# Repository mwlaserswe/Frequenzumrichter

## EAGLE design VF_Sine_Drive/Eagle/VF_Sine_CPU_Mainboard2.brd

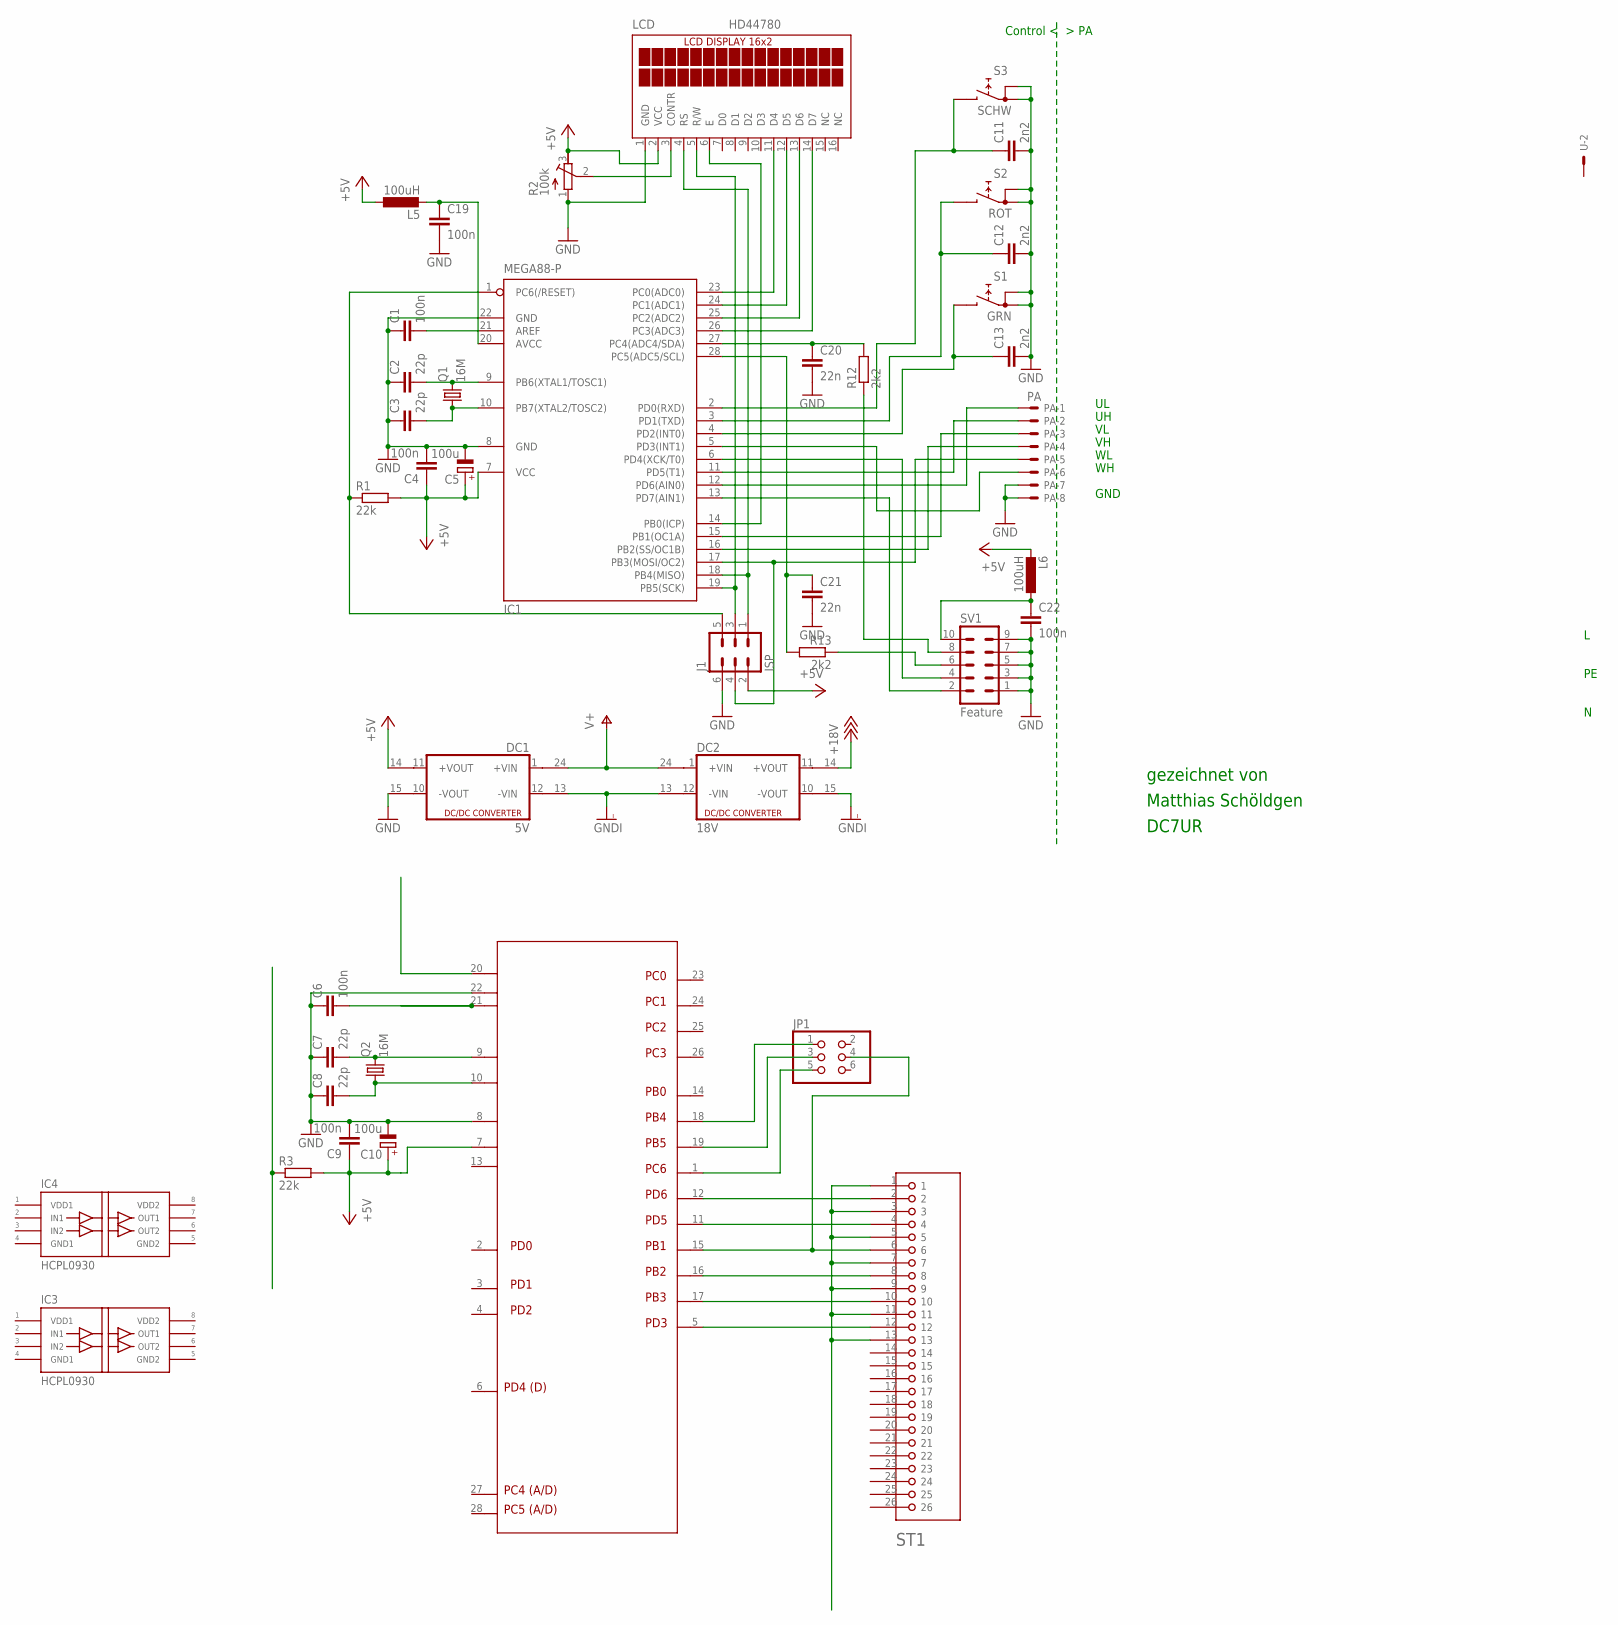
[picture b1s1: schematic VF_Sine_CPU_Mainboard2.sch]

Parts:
C1, C4, C6, C9, C22: 100n; C025-025X050
C2, C3, C7, C8: 22p; C025-025X050
C5, C10: 100u; B45181A
C11, C12, C13: 2n2; C025-025X050
C19: 100n; C050-030X075
C20, C21: 22n; C025-024X044
DC1: 5V; CMK
DC2: 18V; CMK
IC1: MEGA88-P; DIL28-3
IC2: ATMEGA328P_VAR; DIL-28S
IC3, IC4: HCPL0930; SO8
J1: ISP; ML6
JP1: PINHD-2X3; 2X03
L5, L6: 100uH; 0204/5
LCD: HD44780; TUXGR_16X2_R2
PA: PA; 22-23-2081
Q1, Q2: 16M; HC49/S
R1, R3: 22k; 0207/2V
R2: 100k; RTRIM4G/J
R12, R13: 2k2; 0204/5
S1: GRN; RDT1034
S2: ROT; RDT1034
S3: SCHW; RDT1034
ST1: HD-26
SV1: Feature; ML10
U: 5566-2

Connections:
+5V: C4.1, C5.+, C9.1, C10.+, DC1.14 (+VOUT1), IC1.7 (VCC), IC2.7, J1.2, L5.1, L6.2, LCD.2 (VCC), R1.2, R2.3 (A), R3.2
+18V: DC2.14 (+VOUT1)
GND: C1.1, C2.1, C3.1, C4.2, C5.-, C6.1, C7.1, C8.1, C9.2, C10.-, C11.2, C12.2, C13.2, C19.2, C20.2, C21.2, C22.2, DC1.15 (-VOUT1), IC1.8 (GND), IC1.22 (GND), IC2.8, IC2.22, J1.6, LCD.1 (GND), PA.7, PA.8, R2.1 (E), S1.A, S1.A1, S2.A, S2.A1, S3.A, S3.A1, SV1.1, SV1.3, SV1.5, SV1.7, SV1.9
GNDI: DC1.13 (-VIN1), DC2.13 (-VIN1), DC2.15 (-VOUT1)
unnamed: IC1.18 (PB4(MISO)), J1.1, LCD.4 (RS)
unnamed: IC1.19 (PB5(SCK)), J1.3, LCD.5 (R/W)
unnamed: IC1.17 (PB3(MOSI/OC2)), J1.4, PA.5
unnamed: IC1.1 (PC6(/RESET)), J1.5, R1.1
unnamed: IC1.12 (PD6(AIN0)), PA.1
unnamed: IC1.11 (PD5(T1)), PA.2
unnamed: IC1.15 (PB1(OC1A)), PA.3
unnamed: IC1.16 (PB2(SS/OC1B)), PA.4
unnamed: IC1.5 (PD3(INT1)), PA.6
unnamed: IC1.23 (PC0(ADC0)), LCD.11 (D4)
unnamed: IC1.24 (PC1(ADC1)), LCD.12 (D5)
unnamed: IC1.25 (PC2(ADC2)), LCD.13 (D6)
unnamed: C1.2, IC1.21 (AREF)
unnamed: C2.2, IC1.9 (PB6(XTAL1/TOSC1)), Q1.2
unnamed: C3.2, IC1.10 (PB7(XTAL2/TOSC2)), Q1.1
unnamed: IC1.26 (PC3(ADC3)), LCD.14 (D7)
unnamed: IC1.13 (PD7(AIN1)), SV1.2
unnamed: IC1.14 (PB0(ICP)), LCD.6 (E)
unnamed: LCD.3 (CONTR), R2.2 (S)
unnamed: IC1.6 (PD4(XCK/T0)), SV1.4
unnamed: R12.1, SV1.8
unnamed: R13.1, SV1.6
unnamed: C13.1, IC1.4 (PD2(INT0)), S1.B
unnamed: C12.1, IC1.3 (PD1(TXD)), S2.B
unnamed: C11.1, IC1.2 (PD0(RXD)), S3.B
unnamed: ST1.1, ST1.3, ST1.5, ST1.7, ST1.9, ST1.11, ST1.13
unnamed: IC2.12, ST1.2
unnamed: IC2.11, ST1.4
unnamed: IC2.15, JP1.4, ST1.6
unnamed: IC2.16, ST1.8
unnamed: IC2.17, ST1.10
unnamed: IC2.5, ST1.12
unnamed: IC2.18, JP1.1
unnamed: IC2.19, JP1.3
unnamed: IC2.1, JP1.5
unnamed: C19.1, IC1.20 (AVCC), L5.2
unnamed: C20.1, IC1.27 (PC4(ADC4/SDA)), R12.2
unnamed: C21.1, IC1.28 (PC5(ADC5/SCL)), R13.2
unnamed: C6.2, IC2.21
unnamed: C7.2, IC2.9, Q2.2
unnamed: C8.2, IC2.10, Q2.1
unnamed: C22.1, L6.1, SV1.10
V+: DC1.24 (+VIN1), DC2.24 (+VIN1)

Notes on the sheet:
GND
Matthias Schöldgen
gezeichnet von
DC7UR
Control < > PA
PD5
PD6
PB1
PB2
PB3
PD3
PC1
PC0
PC2
PC3
PB4
PB0
PB5
PC6
PD0
PD1
PD2
PD4 (D)
PC4 (A/D)
PC5 (A/D)

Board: 2 copper layers, 42 parts (0 on the bottom side), 46 nets, no tracks yet.

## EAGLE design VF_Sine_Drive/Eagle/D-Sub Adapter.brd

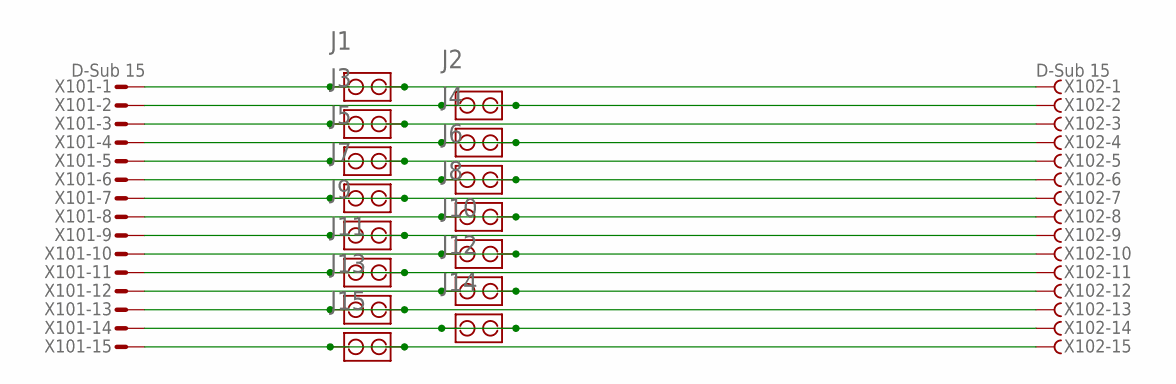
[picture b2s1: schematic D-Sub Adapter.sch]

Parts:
J1, J2, J3, J4, J5, J6, J7, J8, J9, J10, J11, J12, J13, J14, J15: JUMPER
X101: D-Sub 15; M15HP
X102: D-Sub 15; F15HP

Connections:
unnamed: J1.1, J1.2, X101.1, X102.1
unnamed: J2.1, J2.2, X101.2, X102.2
unnamed: J3.1, J3.2, X101.3, X102.3
unnamed: J4.1, J4.2, X101.4, X102.4
unnamed: J5.1, J5.2, X101.5, X102.5
unnamed: J6.1, J6.2, X101.6, X102.6
unnamed: J7.1, J7.2, X101.7, X102.7
unnamed: J8.1, J8.2, X101.8, X102.8
unnamed: J9.1, J9.2, X101.9, X102.9
unnamed: J10.1, J10.2, X101.10, X102.10
unnamed: J11.1, J11.2, X101.11, X102.11
unnamed: J12.1, J12.2, X101.12, X102.12
unnamed: J13.1, J13.2, X101.13, X102.13
unnamed: J14.1, J14.2, X101.14, X102.14
unnamed: J15.1, J15.2, X101.15, X102.15

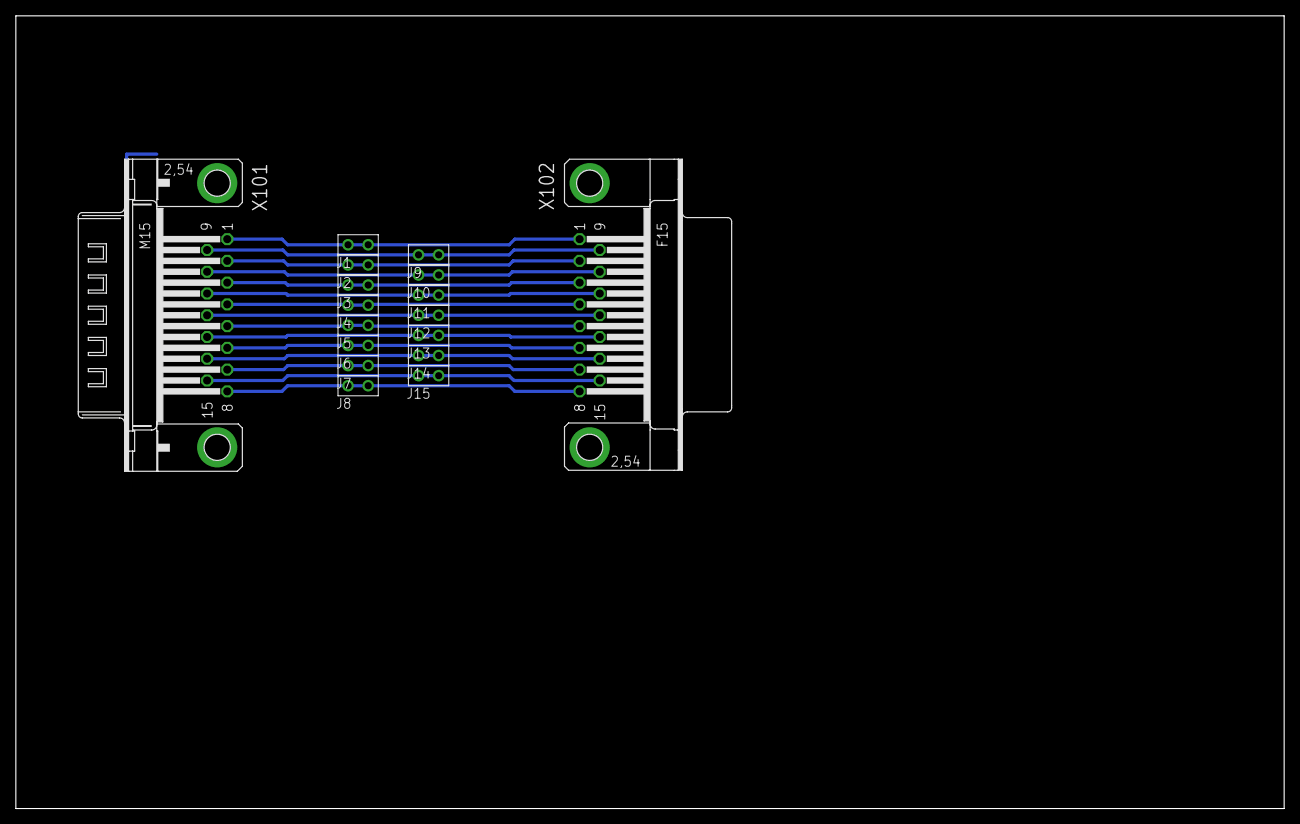
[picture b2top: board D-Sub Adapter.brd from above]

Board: 2 copper layers, 160.0 x 100.0 mm, 17 parts (0 on the bottom side), 15 nets.

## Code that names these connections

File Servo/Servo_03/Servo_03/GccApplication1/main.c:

#include <avr/io.h>
#include <avr/interrupt.h>

#define LED1 5
volatile uint8_t State;


void InitInterrupt (void)
{
	DDRB |= 0x00;

	PCICR |= (1 << PCIE0);
	PCMSK0 |= (1 << PCINT0);

}


// Damit rufe ich den Interrupt auf:

ISR(PCINT0_vect)
{
	if (State == 0)
	{
		PORTD |= (1<<LED1);		// Bit set
		State = 1;
	}
	else
	{
		PORTD &= ~(1<<LED1);	// Bit reset (~ is complement)
		State = 0;
	}
}


int main (void)
{	DDRD = 0b00100000;		// Define Port D Bit 5 as Output
	PORTB = 0b00000001;		// Define Port B Bit 0 as pull up

	
	InitInterrupt();
	sei();

	while(1)
	{
		PORTD &= ~(1 << PD4);
	}
}

////////ATmega8, 16mHz,ein Kanal wird mit einem Ext.Int ausgewertet.
//////
//////#include <avr/io.h>
//////#include <avr/interrupt.h>
//////
//////volatile uint8_t Pulsdauer = 0;
//////
//////void (steigende_Flanke)(void);
//////void (fallende_Flanke)(void);
//////
//////SIGNAL(SIG_INTERRUPT0)
//////{
	//////if( MCUCR == 0x03) // Testen auf steigende Flanke
	//////{
		//////steigende_Flanke();
		//////return;
	//////}
//////
	//////if( MCUCR == 0x02 ) // Testen auf fallende Flanke
	//////{
		//////fallende_Flanke();
		//////return;
	//////}
//////}
//////void (steigende_Flanke)(void)
//////{
	//////TCNT0 = 0; // Timer Reset
	//////TCCR0 = (1<<CS02);  // Timer2 1/256 MCU start
	//////MCUCR = 0x02; // INT0 fallende Flanke
//////}
//////void (fallende_Flanke)(void)
//////{
	//////TCCR0 = 0x00; // Timer2 Stoppen
	//////Pulsdauer = TCNT0; // Timer Wert = Pulsdauer
	//////MCUCR = 0x03; // INT0 auf steigende Flanke
//////}
//////
//////int main(void) {
//////
	////////PD2 Int0 für RC Signal
	//////PORTD = 0x04;       // Pull up on PD2
	//////DDRD = 0xFB;        // PD2 in Rest out
//////
	////////Int0 steigende Flanke / INT0 enable
	//////MCUCR =(1<<ISC01) | (1<<ISC00);
	//////GICR =(1<<INT0);
//////
	//////sei();
//////
	//////for(;;)
	//////{
//////
		//////if (Pulsdauer < 68){"mach was"}
//////
		//////else if (Pulsdauer >= 68 && Pulsdauer < 85){"mach was anderes"}
//////
		//////else if (Pulsdauer >= 85 && Pulsdauer < 110){"mach was anderes"}
//////
		//////else if (Pulsdauer >= 110 && Pulsdauer < 150){"mach was anderes"}
	//////}
//////}




//////// https://www.mikrocontroller.net/attachment/6103/PWM.c 
//////#include <inttypes.h>
//////#include <avr/io.h>
//////#include <avr/interrupt.h>
////////#include <avr/signal.h>
////////#include <ioM8.h>
//////
//////
//////void
//////ioinit (void)
//////{
//////
	///////* PORTB als Ausgang */
	//////DDRB = (1<<PB7) | (1<<PB6) | (1<<PB5) | (1<<PB4)
	//////| (1<<PB3) | (1<<PB2) | (1<<PB1) | (1<<PB0) ;
//////
	///////* PORTB alle LEDs aus */
	//////PORTB = 0xFF ;
//////
	///////* PORTD PD2 als Eingang / Rest als Ausgang */
	//////DDRD = (1<<PD7) | (1<<PD6) | (1<<PD5) | (1<<PD4)
	//////| (1<<PD3) | ~(1<<PD2) | (1<<PD1) | (1<<PD0) ;
	//////
//////
	///////* Int0 steigende Flanke / INT0 enable */
	//////MCUCR = (1<<ISC01) | (1<<ISC00);
	//////GICR = (1<<INT0);
//////
	///////* Timer0 (8Bit) 1/8 MCU Takt */
	//////TCCR0 = (1<<CS01);
	//////
	///////* Timer1 16 Bit 1/8 MCU Takt */
	//////TCCR1B = (1<<CS11);
	//////
	///////* Timer2 8 Bit 1/8 MCU Takt */
	//////TCCR2 = (1<<CS21);
	//////
	///////* Timer1 Overflow */
	//////TIMSK = (1<<TOIE1);
	//////
	///////* enable interrupts */
	//////sei ();
//////}
//////
//////
//////int
//////main (void)
//////{
	//////ioinit ();
//////
	//////for (;;) ;
//////
	//////return (0);
//////}
//////
///////* Timer1 Überlauf für blinkende LEDs an PORTB */
//////SIGNAL(SIG_OVERFLOW1)
//////{
	//////static unsigned char Tick;
	//////Tick++;
//////
	//////if (Tick < 16)
	//////{
		//////PORTB = 0x00;
	//////}
	//////else if (Tick > 16)
	//////{
		//////PORTB = 0xFF;
	//////}
//////
	//////if (Tick > 31)
	//////{
		//////Tick = 0;
	//////}
	//////TCNT1 = 0x04;
//////}
//////
///////* INT0 */
//////SIGNAL(SIG_INTERRUPT0)
//////{
	//////TCNT0 = 0;
	//////TCNT2 = 0;
//////}






















//////// Das ist dieser Link:  https://www.mikrocontroller.net/attachment/6104/RC_SIGNAL4ok4LED.c
//////
//////
//////
///////* ATmega8 mit 8 Mhz */
///////* PORTB 4 LED's gegen VCC */
///////* RC-Signal an PD2 (INT0) */
///////* 1ms Pulsdauer = 31 */
///////* 1,5ms Pulsdauer = 46 */
///////* 2ms Pulsdauer = 62 */
//////
//////
//////#include <inttypes.h>
//////#include <avr/io.h>
//////#include <avr/interrupt.h>
////////#include <avr/signal.h>
////////#include <ioM8.h>
//////
//////#define MEINBIT0 0
//////#define MEINBIT1 1
//////#define MEINBIT2 2
//////#define MEINBIT3 3
//////#define MEINBIT4 4
//////#define MEINBIT5 5
//////#define MEINBIT6 6
//////#define MEINBIT7 7
//////
//////volatile uint8_t Pulsdauer = 0;
//////
//////void (steigende_Flanke)(void);
//////void (fallende_Flanke)(void);
//////
//////void
//////ioinit (void)
//////{
//////
	//////PORTB = 0xFF;
	//////DDRB = 0xFF;
	//////
	//////PORTD = 0x04;       // Pull up on PD2
	//////DDRD = 0xFB;        // PD2 in Rest out
	//////
	//////
	///////* Int0 steigende Flanke / INT0 enable */
	//////MCUCR = (1<<ISC01) | (1<<ISC00);
	//////GICR = (1<<INT0);
	//////
	///////* enable interrupts */
	//////sei ();
//////}
//////
//////int
//////main (void)
//////{
	//////ioinit ();
//////
	//////for (;;)
	//////{
//////
		//////if (Pulsdauer < 32)
		//////{
			//////PORTB = 0xFF;
		//////}
		//////
		//////else if (Pulsdauer > 32 && Pulsdauer < 41)
		//////{
			//////PORTB = 0xFE; // LED PB0 an invertiert, da STK500 gegen VCC
		//////}
		//////
		//////else if (Pulsdauer > 41 && Pulsdauer < 50)
		//////{
			//////PORTB = 0xFC; //LED PB1 und PB0 an, invertiert, da STK500 gegen VCC
		//////}
		//////
		//////else if (Pulsdauer > 50 && Pulsdauer < 59)
		//////{
			//////PORTB = 0xF8; //LED PB2,PB1 und PB0 an, invertiert, da STK500 gegen VCC
		//////}
		//////
		//////else if (Pulsdauer > 59 && Pulsdauer < 68)
		//////{
			//////PORTB = 0xF0; //LED PB3,PB2,PB1 und PB0 an, invertiert, da STK500 gegen VCC
		//////}
		//////
	//////}
	//////;
//////
	//////return (0);
//////}
//////
//////SIGNAL(SIG_INTERRUPT0)
//////{
	//////if( MCUCR == 0x03) // Testen auf steigende Flanke
	//////{
		//////steigende_Flanke();
		//////return;
	//////}
	//////
	//////if( MCUCR == 0x02 ) // Testen auf fallende Flanke
	//////{
		//////fallende_Flanke();
		//////return;
	//////}
//////}
//////void (steigende_Flanke)(void)
//////{
	//////TCNT1 = 0; // Timer Reset
	//////TCCR1B = (1<<CS12);  // Timer1 1/256 MCU start
	//////MCUCR = 0x02; // INT0 fallende Flanke
//////}
//////void (fallende_Flanke)(void)
//////{
	//////TCCR1B = 0x00; // Timer2 Stoppen
	//////Pulsdauer = TCNT1; // Timer Wert = Pulsdauer
	//////MCUCR = 0x03; // INT0 auf steigende Flanke
//////}

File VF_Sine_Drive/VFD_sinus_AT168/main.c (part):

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 *	Hardware and LCD
 *  	------------------
 *      A HD44780 Display is connected to
 * 	LCD Data DB4-7 on PC0-PC3
 *  	LCD E to PB0
 * 	LCD RS to PB4
 *	LCD RW to PB5
 *  Connections have been chosen to not interfere with the six PWM outputs.
 *	Peter Fleury's library is used to drive the LCD and it has been modified
 *	See lcd.h for the settings. Make sure to apply pin and XTAL settings
 *      to LCD.h and set DIVISIONEER in vfd.h according to the formula there
 * 	The default settings are for a 16MHz Crystal.
 *      
 *	Three buttons are connected to PD0 to PD2 (grounding the resp. pin)
 *	Button 0 black cycles through parameters
 *	Button 1 red   decreases selected parameter
 *	Button 2 green increases selected parameter
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 *  The EEPROM set is run on power up
 *      
 *  Frequency and Amplitude control:
 *  when jumper on PD4 is set (grounded) control of Frequency and V/Hz is done
 * 	by analog values from ADC inputs 4 and 5 resp.
 *
 *  Direction control is provided through PD7: 
 *	Attention! 
 *	This drive doesn't measure motor rotation and can't determine wether 
 *  the motor is stopped or not. To change direction you should stop the motor first.
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static void PinChangeIntInit(void)
{
  // Initialize pin change interrupt on direction command pin
  // PD7 is PCINT23
  PCMSK2 = _BV(PCINT23);
  // Enable pin change interrupt on ports with pin change signals
  PCICR = (1 << PCIE2);
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
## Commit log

2018-10-23 SWE: first commit
2018-10-26 Test: Lauflicht mit den grünen LED's auf dem EVK1100
2018-10-26 neuer Kommentar
2018-10-26 Test: Taste drücken, dann geht die entsprechende grüne LED an
2018-12-09 SWE: Viele, viele Änderungen
2018-12-17 SWE: neue Arduino-Projekte
2018-12-17 SWE: unnötige Files löschen
2018-12-17 SWE: Programm besser in Unterprogramme aufteilen
2018-12-28 SWE: D-Sub Testadapter
2018-12-28 SWE: Cleanup
2018-12-28 SWE: Mainboard from Stephan
2018-12-30 SWE: Arduino UNO Layout mit den Ports beschriftet
2018-12-30 SWE: SPS-Zyklus näher an 10ms
2019-02-05 SWE: Update bei Stephan
2020-04-01 SWE: Neues Arduino Projekt: Servo Ansteuerung
2020-04-05 SWE: Servo 1 working
2020-04-05 SWE: Standard Task working
2020-04-06 SWE: testing...
2020-04-07 SWE: Servo working. Ready for layout.
2020-04-12 SWE: Rescue documentation. Pictures suddenly dissappeard
2020-04-12 SWE: Move "Servo" project to separate path
2020-04-12 SWE: Update Docu
